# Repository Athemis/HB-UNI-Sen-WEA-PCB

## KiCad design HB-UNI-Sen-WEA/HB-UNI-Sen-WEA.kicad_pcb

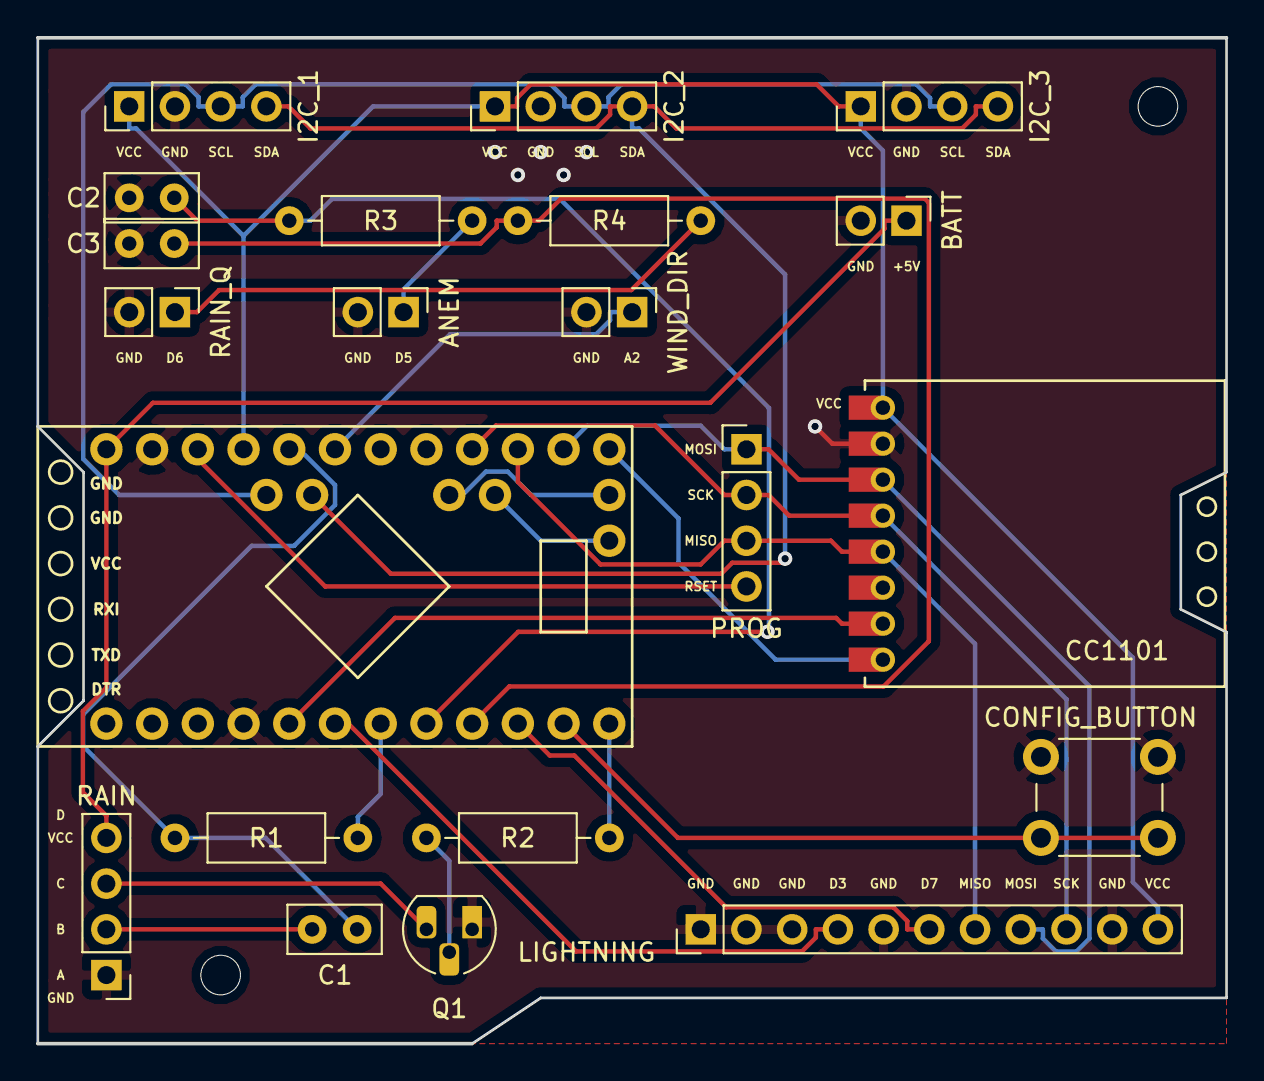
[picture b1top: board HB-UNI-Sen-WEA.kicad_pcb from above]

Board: 2 copper layers, 66.0 x 55.9 mm, 23 parts (0 on the bottom side), 25 nets.

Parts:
C1: 1nF; C_Disc_D5.0mm_W2.5mm_P2.50mm
C2, C3: 100nF; C_Disc_D5.0mm_W2.5mm_P2.50mm
J1: RAIN; PinHeader_1x04_P2.54mm_Vertical
J2: PROG; PinHeader_1x04_P2.54mm_Vertical
J3: WIND_DIR; PinHeader_1x02_P2.54mm_Vertical
J4: I2C_1; PinHeader_1x04_P2.54mm_Vertical
J5: LIGHTNING; PinHeader_1x11_P2.54mm_Vertical
J6: ANEM; PinHeader_1x02_P2.54mm_Vertical
J7: RAIN_Q; PinHeader_1x02_P2.54mm_Vertical
J8: I2C_2; PinHeader_1x04_P2.54mm_Vertical
J9: I2C_3; PinHeader_1x04_P2.54mm_Vertical
J10: BATT; PinHeader_1x02_P2.54mm_Vertical
MH1, MH2: MountingHole_2.2mm_M2
Q1: MPSA13; TO-92_HandSolder
R1: 100K; R_Axial_DIN0207_L6.3mm_D2.5mm_P10.16mm_Horizontal
R2: 10K; R_Axial_DIN0207_L6.3mm_D2.5mm_P10.16mm_Horizontal
R3, R4: 100; R_Axial_DIN0207_L6.3mm_D2.5mm_P10.16mm_Horizontal
SW1: CONFIG_BUTTON; SW_PUSH_6mm_H5mm
U1: ArduinoProMini
U2: CC1101

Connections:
+5V: J1.4, J10.1, U1.12
/A2: J3.1, U1.7
/A3: C1.2, R1.1, U1.8
/B: C1.1, J1.2
/C: J1.3, Q1.3
/D2: U1.17, U2.7
/D3: J5.4, U1.18
/D4: R1.2, U1.19
/D5: C2.2, R3.2, U1.20
/D6: C3.2, R4.2, U1.21
/D7: J5.6, U1.22
/D8: SW1.1, U1.23
/D9: R2.2, U1.24
/MISO: J2.3, J5.7, U1.3, U2.5
/MOSI: J2.1, J5.8, U1.2, U2.3
/RSET: J2.4, U1.10
/SCK: J2.2, J5.9, U1.4, U2.4
/SCL: J4.3, J8.3, J9.3, U1.26
/SDA: J4.4, J8.4, J9.4, U1.25
/SS: U1.1, U2.8
/VCC: J4.1, J5.11, J8.1, J9.1, U1.9, U2.1
GND: C2.1, C3.1, J1.1, J3.2, J4.2, J5.1, J5.2, J5.3, J5.5, J5.10, J6.2, J7.2, J8.2, J9.2, J10.2, Q1.1, SW1.2, U1.11, U1.16, U2.2
unnamed: J6.1, R3.1
unnamed: J7.1, R4.1
unnamed: Q1.2, R2.1

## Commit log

2018-07-31 add README
2018-07-31 add LICENSE
2018-07-31 add mounting holes
2018-07-31 remove uneeded files, add gitignore
2018-07-31 remove uneeded files
2018-07-31 fix typos
2018-07-31 add circuit diagram as pdf
2018-08-07 updated PCB layout
2018-08-07 pcb update
2018-08-07 relicense to CC-BY-SA 4.0
2018-08-08 new pcb routing
